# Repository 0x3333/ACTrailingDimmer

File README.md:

# AC Trailing Edge Dimmer

This is a Trailing Edga MOSFET Dimmer I'm working on. The specs are for 110V AC, not 220V or so, some components values must be changed.

It uses a ATMega 32u4 / Pro Micro module.

The firmware is has not been written yet.

*** THIS HAS NOT BEEN TESTED ***

2023-03-16: Added some changes based on Tim Williams [feedback](https://electronics.stackexchange.com/questions/658777/is-it-right-to-route-ac-l-n-on-different-layers-on-a-pcb/658796#658796) on StackExchange.

[Schematic](.github/schematic.pdf?raw=true)

PCB:

Render:

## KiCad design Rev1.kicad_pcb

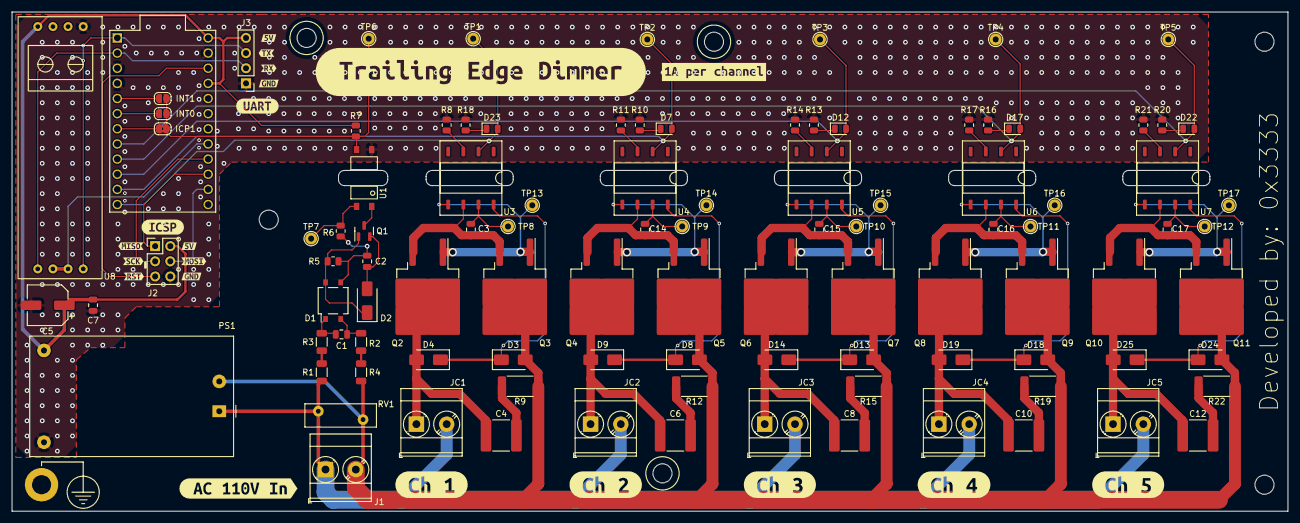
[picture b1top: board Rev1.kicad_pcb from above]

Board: 2 copper layers, 214.0 x 83.7 mm, 129 parts (0 on the bottom side), 69 nets.

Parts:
C1: 1nF/250V; C_0805_2012Metric
C2: 10uF/16V; C_0805_2012Metric
C3, C7, C14, C15, C16, C17: 100nF; C_0805_2012Metric
C4, C6, C8, C10, C12: 22nF X2; C_2220_5650Metric
C5: 47uF; CP_Elec_6.3x5.4
D1: MB6S; TO-269AA
D2, D3, D4, D8, D9, D13, D14, D18, D19, D24, D25: 1N4007; D_SMA
D7, D12, D17, D22, D23: LED; LED_0805_2012Metric
H1, H3, H4, H5, H6, H7: MountingHole; MountingHole_3.2mm_M3_DIN965
H2: MountingHole_Pad; MountingHole_3.2mm_M3_DIN965_Pad
J1: Screw_Terminal_01x02; TerminalBlock_Phoenix_MKDS-3-2-5.08_1x02_P5.08mm_Horizontal
J2: AVR-ISP-6; PinHeader_2x03_P2.54mm_Vertical
J3: UART Debug; PinHeader_1x04_P2.54mm_Vertical
JC1, JC2, JC3, JC4, JC5: Screw_Terminal_01x02; TerminalBlock_Phoenix_MKDS-3-2-5.08_1x02_P5.08mm_Horizontal
JP1: INT1; SolderJumper-2_P1.3mm_Open_RoundedPad1.0x1.5mm
JP2: INT0; SolderJumper-2_P1.3mm_Open_RoundedPad1.0x1.5mm
JP3: ICP1; SolderJumper-2_P1.3mm_Bridged2Bar_RoundedPad1.0x1.5mm
PS1: HLK-PM01; Converter_ACDC_HiLink_HLK-PMxx
Q1: MMBT2222ALT1G; SOT-23
Q2, Q3, Q4, Q5, Q6, Q7, Q8, Q9, Q10, Q11: NCE70T360D; TO-263-2
R1, R2, R3, R4: 110K; R_1206_3216Metric
R5: 47K; R_0805_2012Metric
R6: 1K; R_0805_2012Metric
R7: 10K; R_0805_2012Metric
R8, R11, R14, R17, R21: 470R; R_0805_2012Metric
R9, R12, R15, R19, R22: 220R 1W; R_2512_6332Metric_Pad1.40x3.35mm_HandSolder
R10, R13, R16, R18, R20: 390R; R_0805_2012Metric
RV1: RM10D201KD1IE100; RV_Disc_D12mm_W3.9mm_P7.5mm
TP1, TP2, TP3, TP4, TP5, TP8, TP9, TP10, TP11, TP12, TP13, TP14, TP15, TP16, TP17: TestPoint; TestPoint_THTPad_D2.0mm_Drill1.0mm
TP6, TP7: TestPointZC; TestPoint_THTPad_D2.0mm_Drill1.0mm
U1: VOL617A; WLSOP-4
U2: ProMicro
U3, U4, U5, U6, U7: CPC1596; DIP-8_W8.89mm_SMDSocket_SmallPads
U8: RS485_MODULE
kibuzzard-6410D85E: G***; kibuzzard-6410D85E
kibuzzard-6410D86B: G***; kibuzzard-6410D86B
kibuzzard-6410D800: G***; kibuzzard-6410D800
kibuzzard-6410D834: G***; kibuzzard-6410D834
kibuzzard-6410DCCB: G***; kibuzzard-6410DCCB
kibuzzard-6410DCD5: G***; kibuzzard-6410DCD5
kibuzzard-6410DCDD: G***; kibuzzard-6410DCDD
kibuzzard-6410DCE2: G***; kibuzzard-6410DCE2
kibuzzard-6410DCF5: G***; kibuzzard-6410DCF5
kibuzzard-6410DD03: G***; kibuzzard-6410DD03
kibuzzard-64132D7E: G***; kibuzzard-64132D7E
kibuzzard-64132D73: G***; kibuzzard-64132D73
kibuzzard-64136D9F: G***; kibuzzard-64136D9F
kibuzzard-64136DB8: G***; kibuzzard-64136DB8
kibuzzard-64136DD3: G***; kibuzzard-64136DD3
kibuzzard-64136DE0: G***; kibuzzard-64136DE0
kibuzzard-64136DEA: G***; kibuzzard-64136DEA
kibuzzard-641373F0: G***; kibuzzard-641373F0
kibuzzard-64133859: G***; kibuzzard-64133859
kibuzzard-64137421: G***; kibuzzard-64137421

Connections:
+5V: C5.1, C7.1, J2.2 (VCC), J3.4, PS1.4 (+Vout), R7.2, U2.21 (VCC), U2.24 (RAW), U8.4 (VCC)
/AC_L: J1.1, JC1.2, JC2.2, JC3.2, JC4.2, JC5.2, PS1.1 (AC/L), R1.1, RV1.1
/AC_N: D3.2 (A), D8.2 (A), D13.2 (A), D18.2 (A), D24.2 (A), J1.2, PS1.2 (AC/N), Q3.2 (D), Q5.2 (D), Q7.2 (D), Q9.2 (D), Q11.2 (D), R2.1, R9.2, R12.2, R15.2, R19.2, R22.2, RV1.2
/Sheetname: Dimmer Channel 1/LOAD: C4.1, D4.2 (A), JC1.1, Q2.2 (D)
/Sheetname: Dimmer Channel 1/Virtual GND: C3.2, Q2.3 (S), Q3.3 (S), U3.6 (B)
/Sheetname: Dimmer Channel 2/LOAD: C6.1, D9.2 (A), JC2.1, Q4.2 (D)
/Sheetname: Dimmer Channel 2/Virtual GND: C14.2, Q4.3 (S), Q5.3 (S), U4.6 (B)
/Sheetname: Dimmer Channel 3/LOAD: C8.1, D14.2 (A), JC3.1, Q6.2 (D)
/Sheetname: Dimmer Channel 3/Virtual GND: C15.2, Q6.3 (S), Q7.3 (S), U5.6 (B)
/Sheetname: Dimmer Channel 4/LOAD: C10.1, D19.2 (A), JC4.1, Q8.2 (D)
/Sheetname: Dimmer Channel 4/Virtual GND: C16.2, Q8.3 (S), Q9.3 (S), U6.6 (B)
/Sheetname: Dimmer Channel 5/LOAD: C12.1, D25.2 (A), JC5.1, Q10.2 (D)
/Sheetname: Dimmer Channel 5/Virtual GND: C17.2, Q10.3 (S), Q11.3 (S), U7.6 (B)
GND: C5.2, C7.2, J2.6 (GND), J3.1, PS1.3 (-Vout), R8.1, R10.1, R11.1, R13.1, R14.1, R16.1, R17.1, R18.1, R20.1, R21.1, U1.3, U2.3 (GND), U2.4 (GND), U2.23 (GND), U8.1 (GND)
ME: U2.17 (PF7/D18/ADC7), U8.6 (~RE), U8.7 (DE)
MISO: J2.1 (MISO), U2.15 (PB3/D14/MISO)
MOSI: J2.4 (MOSI), U2.14 (PB2/D16/MOSI)
unnamed: C1.1, D1.1, R3.2
unnamed: C1.2, D1.2, R4.2
unnamed: C4.2, R9.1
unnamed: C6.2, R12.1
unnamed: C8.2, R15.1
unnamed: C10.2, R19.1
unnamed: C12.2, R22.1
unnamed: C2.1, D1.3 (+), R5.2, R6.1
unnamed: D1.4 (-), D2.1 (K), Q1.1 (B), R5.1
unnamed: C2.2, D2.2 (A), Q1.2 (E)
unnamed: D3.1 (K), D4.1 (K), U3.8 (A)
unnamed: D7.1 (K), R10.2
unnamed: D8.1 (K), D9.1 (K), U4.8 (A)
unnamed: D12.1 (K), R13.2
unnamed: D13.1 (K), D14.1 (K), U5.8 (A)
unnamed: D17.1 (K), R16.2
unnamed: D18.1 (K), D19.1 (K), U6.8 (A)
unnamed: D22.1 (K), R20.2
unnamed: D23.1 (K), R18.2
unnamed: D24.1 (K), D25.1 (K), U7.8 (A)
unnamed: JP3.2 (B), U2.7 (PD4/D4/ADC8/ICP1)
unnamed: Q1.3 (C), U1.2
unnamed: Q2.1 (G), Q3.1 (G), TP13.1, U3.5 (G)
unnamed: Q4.1 (G), Q5.1 (G), TP14.1, U4.5 (G)
unnamed: Q6.1 (G), Q7.1 (G), TP15.1, U5.5 (G)
unnamed: Q8.1 (G), Q9.1 (G), TP16.1, U6.5 (G)
unnamed: Q10.1 (G), Q11.1 (G), TP17.1, U7.5 (G)
unnamed: R1.2, R3.1
unnamed: R2.2, R4.1
unnamed: R6.2, TP7.1, U1.1
unnamed: C3.1, TP8.1, U3.7 (C)
unnamed: R8.2, U3.3 (LED-)
unnamed: C14.1, TP9.1, U4.7 (C)
unnamed: R11.2, U4.3 (LED-)
unnamed: C15.1, TP10.1, U5.7 (C)
unnamed: R14.2, U5.3 (LED-)
unnamed: C16.1, TP11.1, U6.7 (C)
unnamed: R17.2, U6.3 (LED-)
unnamed: C17.1, TP12.1, U7.7 (C)
unnamed: R21.2, U7.3 (LED-)
RX: J3.2, U2.2 (PD2/D0/RXD1), U8.5 (RO)
SCK: J2.3 (SCK), U2.16 (PB1/D15/SCK)
SCL: JP2.2 (B), U2.6 (PD0/D3/SCL)
SDA: JP1.2 (B), U2.5 (PD1/D2/SDA)
TRG_1: D23.2 (A), TP1.1, U2.12 (PB5/D9/ADC12), U3.2 (LED+)
TRG_2: D7.2 (A), TP2.1, U2.11 (PB4/D8/ADC11), U4.2 (LED+)
TRG_3: D12.2 (A), TP3.1, U2.10 (PE6/D7/INT6/AIN0), U5.2 (LED+)
TRG_4: D17.2 (A), TP4.1, U2.9 (PD7/D6/ADC10), U6.2 (LED+)
TRG_5: D22.2 (A), TP5.1, U2.8 (PC6/D5), U7.2 (LED+)
TX: J3.3, U2.1 (PD3/D1/TXD1), U8.8 (DI)
ZC: JP1.1 (A), JP2.1 (A), JP3.1 (A), R7.1, TP6.1, U1.4
/RST: J2.5 (~RST), U2.22 (RST)

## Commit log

2023-03-15 Initial import.
2023-03-15 Added README.md
2023-03-15 Added schematic.
2023-03-16 Added changes based on Tim Williams feedback on StackExchange.
2023-04-04 Added some test points. Added RS-485 Module. Updated PBC.
2023-04-04 Added stitching vias.
2023-04-04 Updated Readme.
